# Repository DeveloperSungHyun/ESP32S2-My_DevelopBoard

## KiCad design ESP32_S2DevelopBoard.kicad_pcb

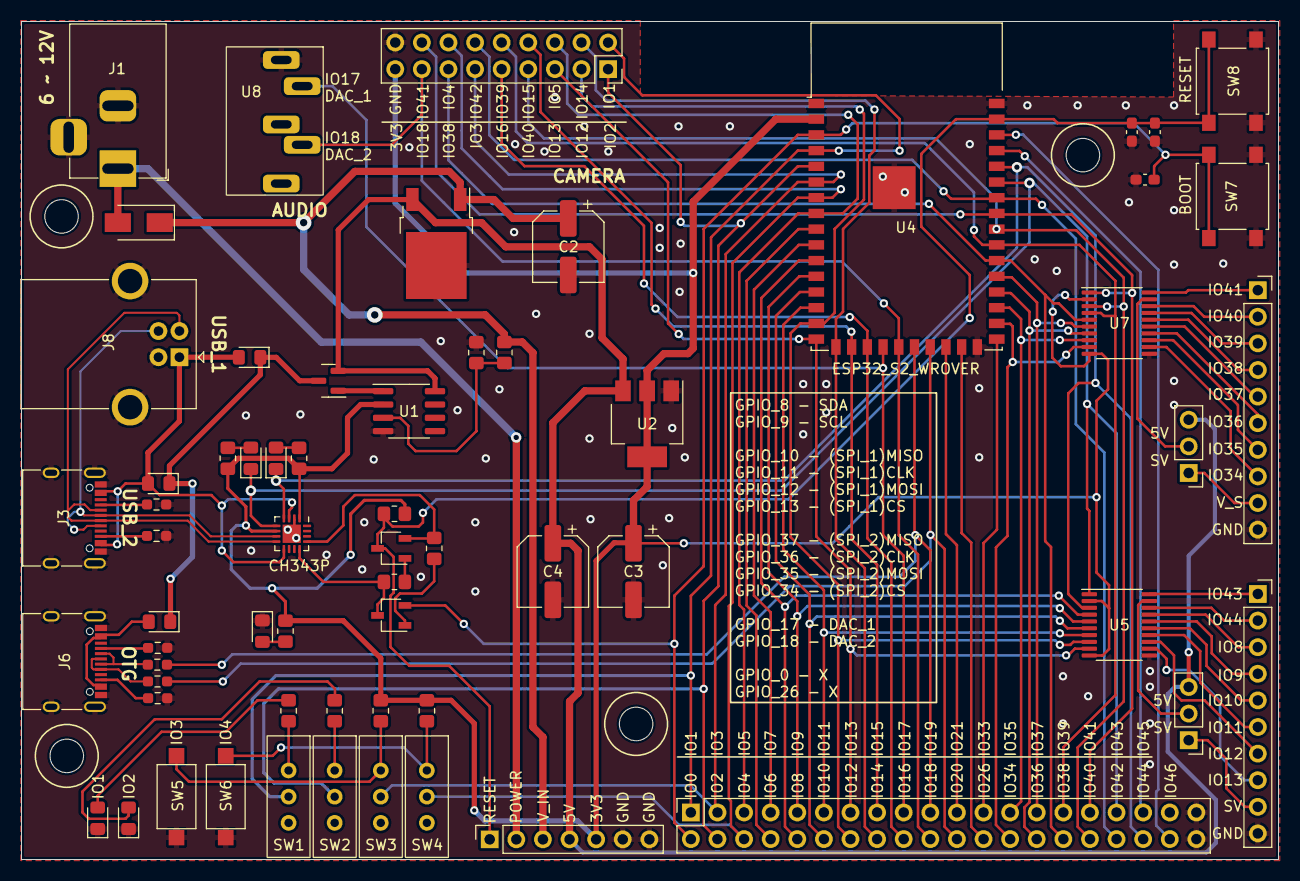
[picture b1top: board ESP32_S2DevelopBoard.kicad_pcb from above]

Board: 2 copper layers, 120.0 x 80.0 mm, 63 parts (0 on the bottom side), 89 nets.

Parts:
C2, C3, C4: 47uF; CP_Elec_6.3x5.7
C7, C8, C9: 100nF; C_0603_1608Metric_Pad1.08x0.95mm_HandSolder
D1: D; D_SMA
D3, D4, D5: D_Schottky; D_0805_2012Metric_Pad1.15x1.40mm_HandSolder
D6, D7, D8, D11, D12: LED; LED_0805_2012Metric_Pad1.15x1.40mm_HandSolder
J1: POWER; BarrelJack_Horizontal
J2, J4: LEVEL_CON; PinSocket_1x10_P2.54mm_Vertical
J3, J6: USB_C_Receptacle_USB2.0; USB_C_Receptacle_XKB_U262-16XN-4BVC11
J5: GPIO_HEADER; PinSocket_2x20_P2.54mm_Vertical
J8: USB_B; USB_B_OST_USB-B1HSxx_Horizontal
J10, J13: v_selection; PinHeader_1x03_P2.54mm_Vertical
J11: Fun; PinSocket_1x07_P2.54mm_Vertical
J14: CAM; PinSocket_2x09_P2.54mm_Vertical
Q1: VP0610T; SOT-23
Q2, Q3: J3Y; TSOT-23
R3, R4, R7, R8: 5.1K; R_0603_1608Metric_Pad0.98x0.95mm_HandSolder
R5, R6, R11, R12, R13, R14, R15, R16, R17, R18, R19, R20: 10K; R_0805_2012Metric_Pad1.20x1.40mm_HandSolder
R9, R10: 27; R_0603_1608Metric_Pad0.98x0.95mm_HandSolder
SW1, SW2, SW3, SW4: SW_SPDT; switch_3pin_1C2T
SW5, SW6: TEST_BT; SW_SPST_CK_RS282G05A3
SW7: BOOT_BT; SW_SPST_B3S-1000
SW8: RES_BT; SW_SPST_B3S-1000
U1: LM358; SOIC-8_3.9x4.9mm_P1.27mm
U2: AZ1117-3.3; SOT-223-3_TabPin2
U3: L7805; TO-252-2
U4: ESP32-S2-WROVER
U5, U7: TXS0108EPW; TSSOP-20_4.4x6.5mm_P0.65mm
U6: CH343P; QFN-16-1EP_3x3mm_P0.5mm_EP1.75x1.75mm
U8: PJ-325_AudioJack; PJ-325

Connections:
+3V3: C3.1, J11.5, J14.17, R11.2, R15.2, R16.2, R17.2, R19.1, R20.1, U1.2 (-), U2.2 (VO), U4.2 (3V3), U5.2 (VCCA), U5.10 (OE), U6.1 (VIO), U6.6 (V3), U7.2 (VCCA), U7.10 (OE)
+5V: C4.1, J10.3, J11.4, J13.3, Q1.2 (S), U1.8 (V+), U2.3 (VI), U3.3 (OUT)
/HREF: J5.6, J14.14, SW4.2 (B), U4.7 (IO04)
/IO0: C9.1, J5.2, Q3.2 (E), SW7.1, U4.3 (IO00)
/IO1: J5.1, J14.2, SW1.2 (B), U4.4 (IO01)
/IO2: J5.4, J14.1, SW2.2 (B), U4.5 (IO02)
/IO3: J5.3, J14.11, SW3.2 (B), U4.6 (IO03)
/IO5: J5.5, J14.6, U4.8 (IO05)
/IO6: J5.8, U4.9 (IO06)
/IO7: J5.7, U4.10 (IO07)
/IO8: J5.10, U4.11 (IO08), U5.4 (A3)
/IO9: J5.9, U4.12 (IO09), U5.5 (A4)
/IO10: J5.12, U4.13 (IO10), U5.6 (A5)
/IO11: J5.11, U4.14 (IO11), U5.7 (A6)
/IO12: J5.14, J14.3, U4.15 (IO12), U5.8 (A7)
/IO13: J5.13, J14.5, U4.16 (IO13), U5.9 (A8)
/IO14: J5.16, J14.4, U4.17 (IO14)
/IO15: J5.15, J14.8, U4.18 (IO15)
/IO16: J5.18, J14.9, U4.19 (IO16)
/IO17: J5.17, U4.20 (IO17), U8.5 (L)
/IO18: J5.20, J14.15, U4.21 (IO18), U8.3 (R)
/IO19: J5.19, R10.2, U4.22 (USB_D-)
/IO20: J5.22, R9.2, U4.23 (USB_D+)
/IO21: J5.21, U4.24 (IO21)
/IO26: J5.24, U4.25 (IO26)
/IO33: J5.23, U4.27 (IO33)
/IO34: J5.26, U4.28 (IO34), U7.9 (A8)
/IO35: J5.25, U4.29 (IO35), U7.8 (A7)
/IO36: J5.28, U4.30 (IO36), U7.7 (A6)
/IO37: J5.27, U4.31 (IO37), U7.6 (A5)
/IO38: J5.30, J14.13, U4.32 (IO38), U7.5 (A4)
/IO39: J5.29, J14.10, U4.33 (IO39), U7.4 (A3)
/IO40: J5.32, J14.7, U4.34 (IO40), U7.3 (A2)
/IO41: J5.31, J14.16, U4.35 (IO41), U7.1 (A1)
/IO42: J5.34, J14.12, U4.36 (IO42)
/IO43: D12.1 (K), J5.33, U4.37 (TXD0), U5.1 (A1), U6.5 (RXD)
/IO44: D11.1 (K), J5.36, U4.38 (RXD0), U5.3 (A2), U6.4 (TXD)
/IO45: J5.35, U4.39 (IO45)
/IO46: J5.38, U4.40 (IO46)
/POWER: D1.2 (A), J1.1, J11.2
/RESET: C7.1, C8.1, J11.1, Q2.3 (C), R15.1, SW8.1, U4.41 (EN)
/USB_5V: D3.1 (K), D4.1 (K), D5.1 (K), Q1.3 (D)
/USB_COM+: J3.A6 (D+), J3.B6 (D+), J8.3 (D+), U6.7 (UD+)
/USB_COM-: J3.A7 (D-), J3.B7 (D-), J8.2 (D-), U6.8 (UD-)
/USB_OTG+: J6.A6 (D+), J6.B6 (D+), R9.1
/USB_OTG-: J6.A7 (D-), J6.B7 (D-), R10.1
/VBUS_1: D3.2 (A), D5.2 (A), J3.A4 (VBUS), J3.A9 (VBUS), J3.B4 (VBUS), J3.B9 (VBUS), J8.1 (VBUS), U6.3 (VDD5), U6.9 (VBUS)
/Vin: C2.1, D1.1 (K), J11.3, R5.1, U3.1 (IN)
/_IO8: J2.3, U5.17 (B3)
/_IO9: J2.4, U5.16 (B4)
/_IO10: J2.5, U5.15 (B5)
/_IO11: J2.6, U5.14 (B6)
/_IO12: J2.7, U5.13 (B7)
/_IO13: J2.8, U5.12 (B8)
/_IO34: J4.8, U7.12 (B8)
/_IO35: J4.7, U7.13 (B7)
/_IO36: J4.6, U7.14 (B6)
/_IO37: J4.5, U7.15 (B5)
/_IO38: J4.4, U7.16 (B4)
/_IO39: J4.3, U7.17 (B3)
/_IO40: J4.2, U7.18 (B2)
/_IO41: J4.1, U7.20 (B1)
/_IO43: J2.1, U5.20 (B1)
/_IO44: J2.2, U5.18 (B2)
/signal_v1: J2.9, J10.1
/signal_v2: J4.9, J13.1
GND: C2.2, C3.2, C4.2, C7.2, C8.2, C9.2, D6.1 (K), D7.1 (K), D8.1 (K), J1.2, J1.3, J2.10, J3.A1 (GND), J3.A12 (GND), J3.B1 (GND), J3.B12 (GND), J3.S1 (SHIELD), J4.10, J5.39, J5.40, J6.A1 (GND), J6.A12 (GND), J6.B1 (GND), J6.B12 (GND), J6.S1 (SHIELD), J8.4 (GND), J8.5 (Shield), J11.6, J11.7, J14.18, R3.2, R4.2, R6.1, R7.2, R8.2, SW5.2, SW6.2, SW7.2, SW8.2, U1.4 (V-), U2.1 (GND), U3.2 (GND), U4.1 (GND), U4.26 (GND), U4.42 (GND), U4.43 (GND), U5.11 (GND), U6.2 (GND), U6.17 (GND), U7.11 (GND), U8.1 (GND)
unnamed: D4.2 (A), J6.A4 (VBUS), J6.A9 (VBUS), J6.B4 (VBUS), J6.B9 (VBUS)
unnamed: D6.2 (A), R11.1
unnamed: D7.2 (A), R12.1
unnamed: D8.2 (A), R13.1
unnamed: D11.2 (A), R16.1
unnamed: D12.2 (A), R17.1
unnamed: J3.A5 (CC1), R3.1
unnamed: J3.B5 (CC2), R4.1
unnamed: J6.A5 (CC1), R7.1
unnamed: J6.B5 (CC2), R8.1
unnamed: J10.2, U5.19 (VCCB)
unnamed: J13.2, U7.19 (VCCB)
unnamed: Q1.1 (G), U1.1
unnamed: Q2.1 (B), R14.1
unnamed: Q2.2 (E), R18.2, U6.13 (RTS)
unnamed: Q3.1 (B), R18.1
unnamed: Q3.3 (C), R14.2, U6.12 (DTR)
unnamed: R12.2, SW1.1 (A)
unnamed: R13.2, SW2.1 (A)
unnamed: R19.2, SW3.1 (A), SW5.1
unnamed: R20.2, SW4.1 (A), SW6.1
unnamed: R5.2, R6.2, U1.3 (+)

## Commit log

2023-12-26 Create README.md
    test
2024-01-30 version 1.0.0
